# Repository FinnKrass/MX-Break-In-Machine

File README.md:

# MX Style Switch Break In Machine

Repository is still a work in progress!

A unique take on the switch break in machine intended to streamline the process and maximise outcomes. Useful for those who want to improve the sound and feeling of MX style keyboard switches that come scratchy/inconsistent from the factory.

**Table of Contents:**

- [Main README](#mx-style-switch-break-in-machine)
  
  - [Background](#background)
  
  - [Features](#features)
  
  - [To Do](#to-do)
  
  - [References & Thanks](#references--thanks)

- [Bill of Materials - Hardware](https://github.com/FinnKrass/MX-Break-In-Machine/blob/main/BoM/Bill-of-Materials-(Hardware).md#bill-of-materials-hardware)
  
  - [Hardware](https://github.com/FinnKrass/MX-Break-In-Machine/blob/main/BoM/Bill-of-Materials-(Hardware).md#hardware)
  
  - [Fasteners](https://github.com/FinnKrass/MX-Break-In-Machine/blob/main/BoM/Bill-of-Materials-(Hardware).md#fasteners)

- [Making Your Own](https://github.com/FinnKrass/MX-Break-In-Machine/blob/main/Documentation/Making-Your-Own.md#making-your-own)
  
  - [Printing](https://github.com/FinnKrass/MX-Break-In-Machine/blob/main/Documentation/Making-Your-Own.md#printing)
    
    - [Print BoM](https://github.com/FinnKrass/MX-Break-In-Machine/blob/main/Documentation/Making-Your-Own.md#print-bom)
  
  - [Additional Hardware](https://github.com/FinnKrass/MX-Break-In-Machine/blob/main/Documentation/Making-Your-Own.md#additional-hardware)
    
    - [Fasteners](https://github.com/FinnKrass/MX-Break-In-Machine/blob/main/Documentation/Making-Your-Own.md#fasteners)
  
  - [Assembly](https://github.com/FinnKrass/MX-Break-In-Machine/blob/main/Documentation/Making-Your-Own.md#assembly)
    
    - [Tools Needed](https://github.com/FinnKrass/MX-Break-In-Machine/blob/main/Documentation/Making-Your-Own.md#tools-needed)
    
    - [Prepare Motor & Limit Switch](https://github.com/FinnKrass/MX-Break-In-Machine/blob/main/Documentation/Making-Your-Own.md#preparing-the-motor--limit-switch)
    
    - [Prepare Motor Assembly](https://github.com/FinnKrass/MX-Break-In-Machine/blob/main/Documentation/Making-Your-Own.md#prepare-the-motor-assembly)
    
    - [Prepare the Pistons](https://github.com/FinnKrass/MX-Break-In-Machine/blob/main/Documentation/Making-Your-Own.md#prepare-the-pistons)
    
    - [Install the Pistons](https://github.com/FinnKrass/MX-Break-In-Machine/blob/main/Documentation/Making-Your-Own.md#install-the-pistons)
    
    - [Install the Motor Assembly](https://github.com/FinnKrass/MX-Break-In-Machine/blob/main/Documentation/Making-Your-Own.md#install-the-motor-assembly)
    
    - [Install the PCB](https://github.com/FinnKrass/MX-Break-In-Machine/blob/main/Documentation/Making-Your-Own.md#install-the-pcb)
  
  - [Testing & Notes](https://github.com/FinnKrass/MX-Break-In-Machine/blob/main/Documentation/Making-Your-Own.md#testing--notes)

- [Making the PCB](https://github.com/FinnKrass/MX-Break-In-Machine/blob/main/Documentation/Making-The-PCB.md)
  
  - [Notes](https://github.com/FinnKrass/MX-Break-In-Machine/blob/main/Documentation/Making-The-PCB.md#notes)
  
  - [To Do](https://github.com/FinnKrass/MX-Break-In-Machine/blob/main/Documentation/Making-The-PCB.md#to-do)
  
  - [Ordering from JLCPCB](https://github.com/FinnKrass/MX-Break-In-Machine/blob/main/Documentation/Making-The-PCB.md#ordering-from-jlcpcb)

## Background

This project started when I first fell in love with Cherry MX Black's. I wanted a way to break in the switches for all of my builds, but had absolutely no understanding of electronics and CAD at the time, so took it upon myself to learn how to use Fusion360 and eventually design a circuit. Once the design had come together, I started selling broken in switches with a fleet of these machines running around the clock, which helped me vet the design and iron out any problems as well as optimize certain things to make the labor involved with operating and maintaining the machines easier. I worked on this project on and off over about a year and was planning to sell the machines themselves once they were in a state I was proud of, but some life events got in the way, so I've decided to work back and open source it for others to enjoy as much as I have.

## Features

The machine is quite rugged, I've had customers request their switches broken in for 2.5 million + actuations and the machines have handled that no problem. For good measure, I give them 1 hour break every 12 hours, and have had machines comfortably surpass total lifetime actuations of 75 million. This isn't guaranteed of course, it depends on a plethora of variables, including materials used to print, print profiles, the motor manufacturer, bearing quality etc. Regardless, here is a list of features:

- Linear bearings (inspired by Feng Studio's machine)
  
  - Eliminate plastic on plastic friction
  - Ensure the pistons remain aligned, applying even force on all switches

- Full capacity (64 switches) off centre operation.

- Noise reducing plates
  
  - The biggest issue I had with the machines was the noise. To fix that, rear plates were integrated into the design that would be printed in a flexible material (95A TPU) to dampen the noise produced by the switches colliding with the back walls and pistons.
  - An off centre version of this was introduced later on. There are two models for this; one which attaches to the piston, and one which rests against the back wall. The intention is to operate in off centre at all times.

- USB Power Delivery compatible controller & power supply.

- 128x64 OLED display for information on progress.

- Actuation counter with programmable profiles to disable/enable the motor after *x* number of actuations. Currently programmed to turn off after 250,000 actuations to ensure an even distribution of off centre actuations on all 4 sides.

- Two speeds can be selected via a switch on the PCB.

- Rugged 24V motor, capable 564 actuations/minute. (Faster is not recommended)

- Non-volatile flash memory, will recall number of actuations recorded in the event of power loss.

Here are a few video's showing off the operation. [Video A](https://youtu.be/W0hglbHXOGw), [Video B](https://youtu.be/-IIjR5GEPkg).

Some older video's of their operation can be found [here](https://youtube.com/shorts/SL5bj8C431c) and [here](https://youtube.com/shorts/yf9J68zrslU).

## To-Do

- [ ] Finalise documentation
  
  - [ ] User guide and tips on operating the machine
  
  - [ ] General clean up, more coherent structure.

- [ ] Acceptable print tolerance specifications

- [x] Piston bearing socket tolerance calibration print

- [ ] PCB BoM optimisations (more details in PCB doc)

- [ ] PCB BoM sheet for mouser to automate adding to cart (should be done very soon)

## References & Thanks

The individual who helped me most requested not to be named, but a deep thank you goes out to them for the help they have provided me and continue to provide to the community. Their help is the reason I became more interested in the intricacies of electronics, and that passion has continued far beyond this project now. 

[Kee Keen's open source break in machine](https://github.com/keekeen/MX-Switch-Break-In-Machine/tree/main) helped me greatly in the beginning, definitely check it out if you're interested in the roots of this project!

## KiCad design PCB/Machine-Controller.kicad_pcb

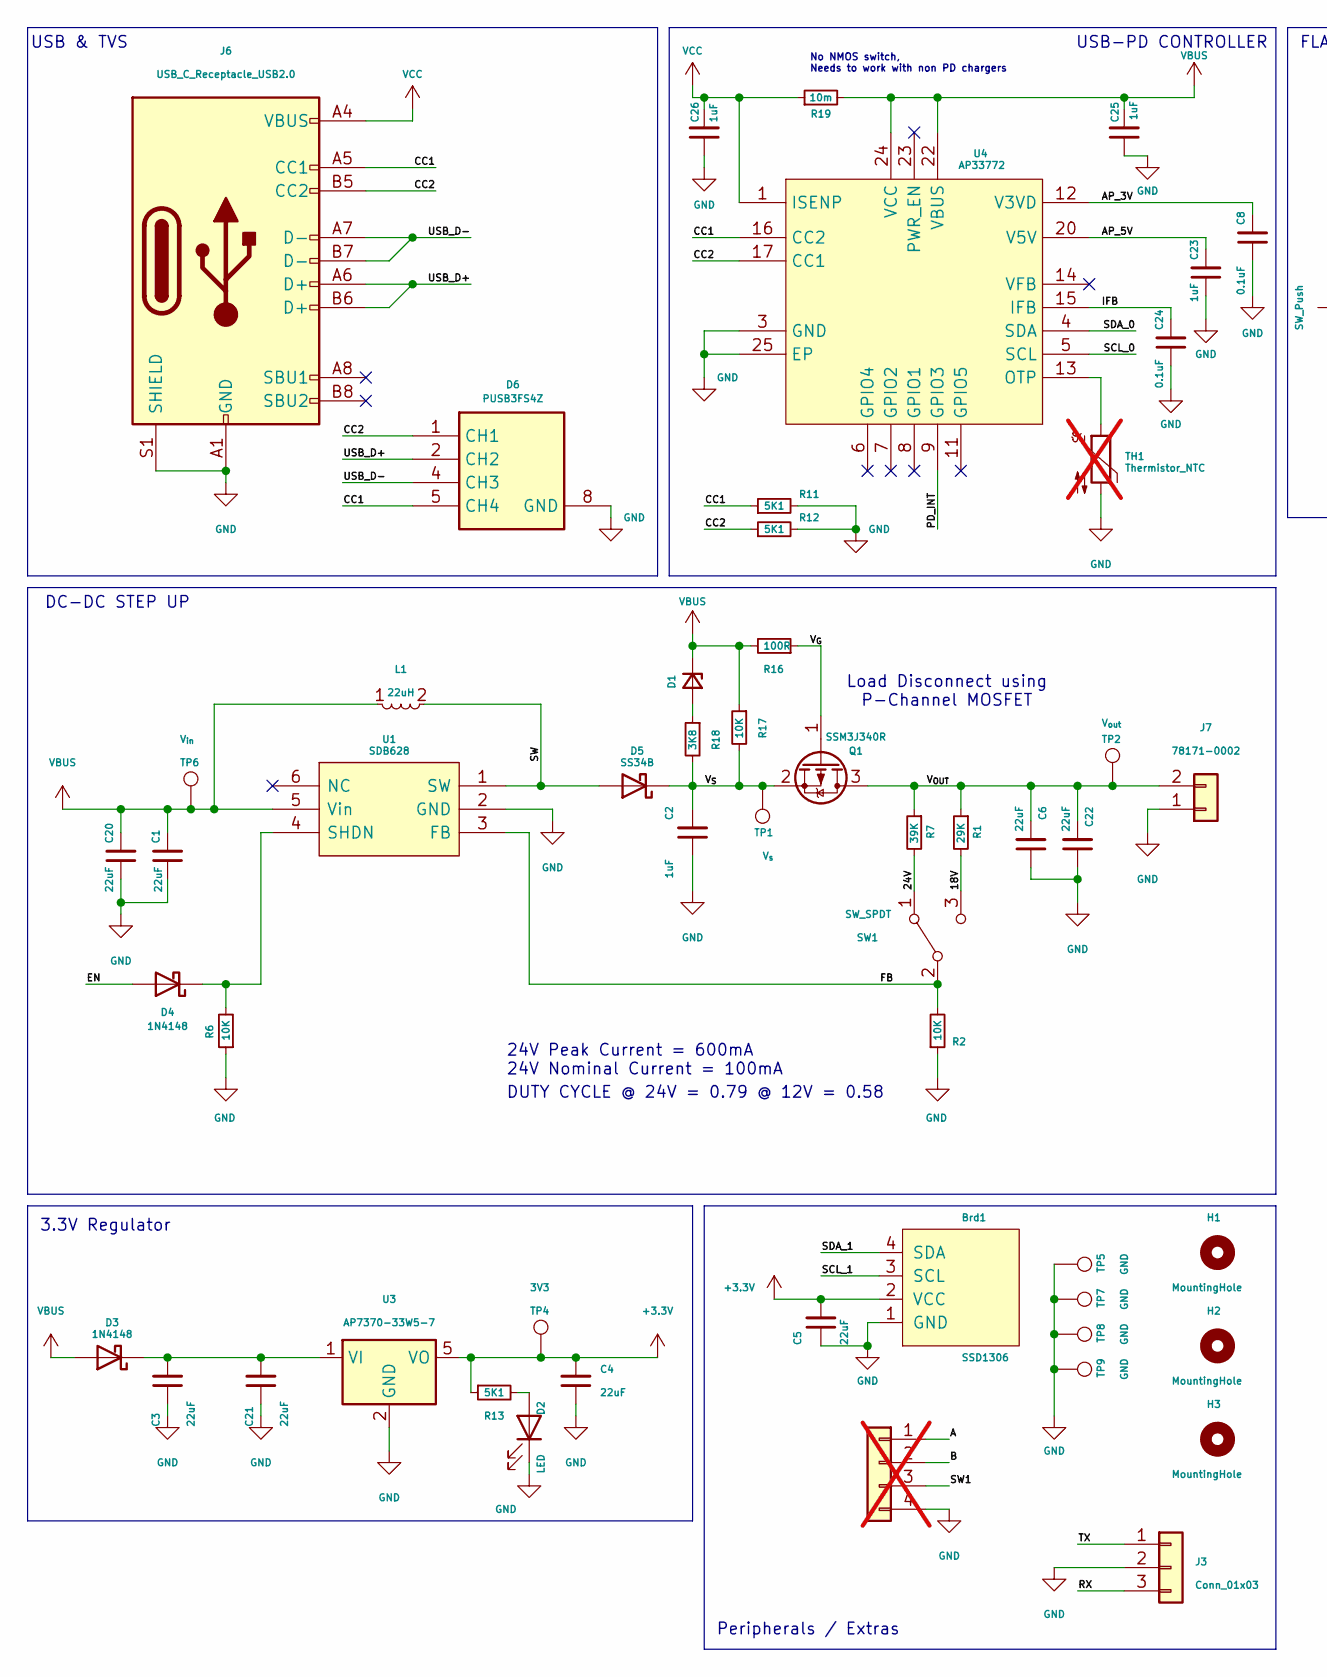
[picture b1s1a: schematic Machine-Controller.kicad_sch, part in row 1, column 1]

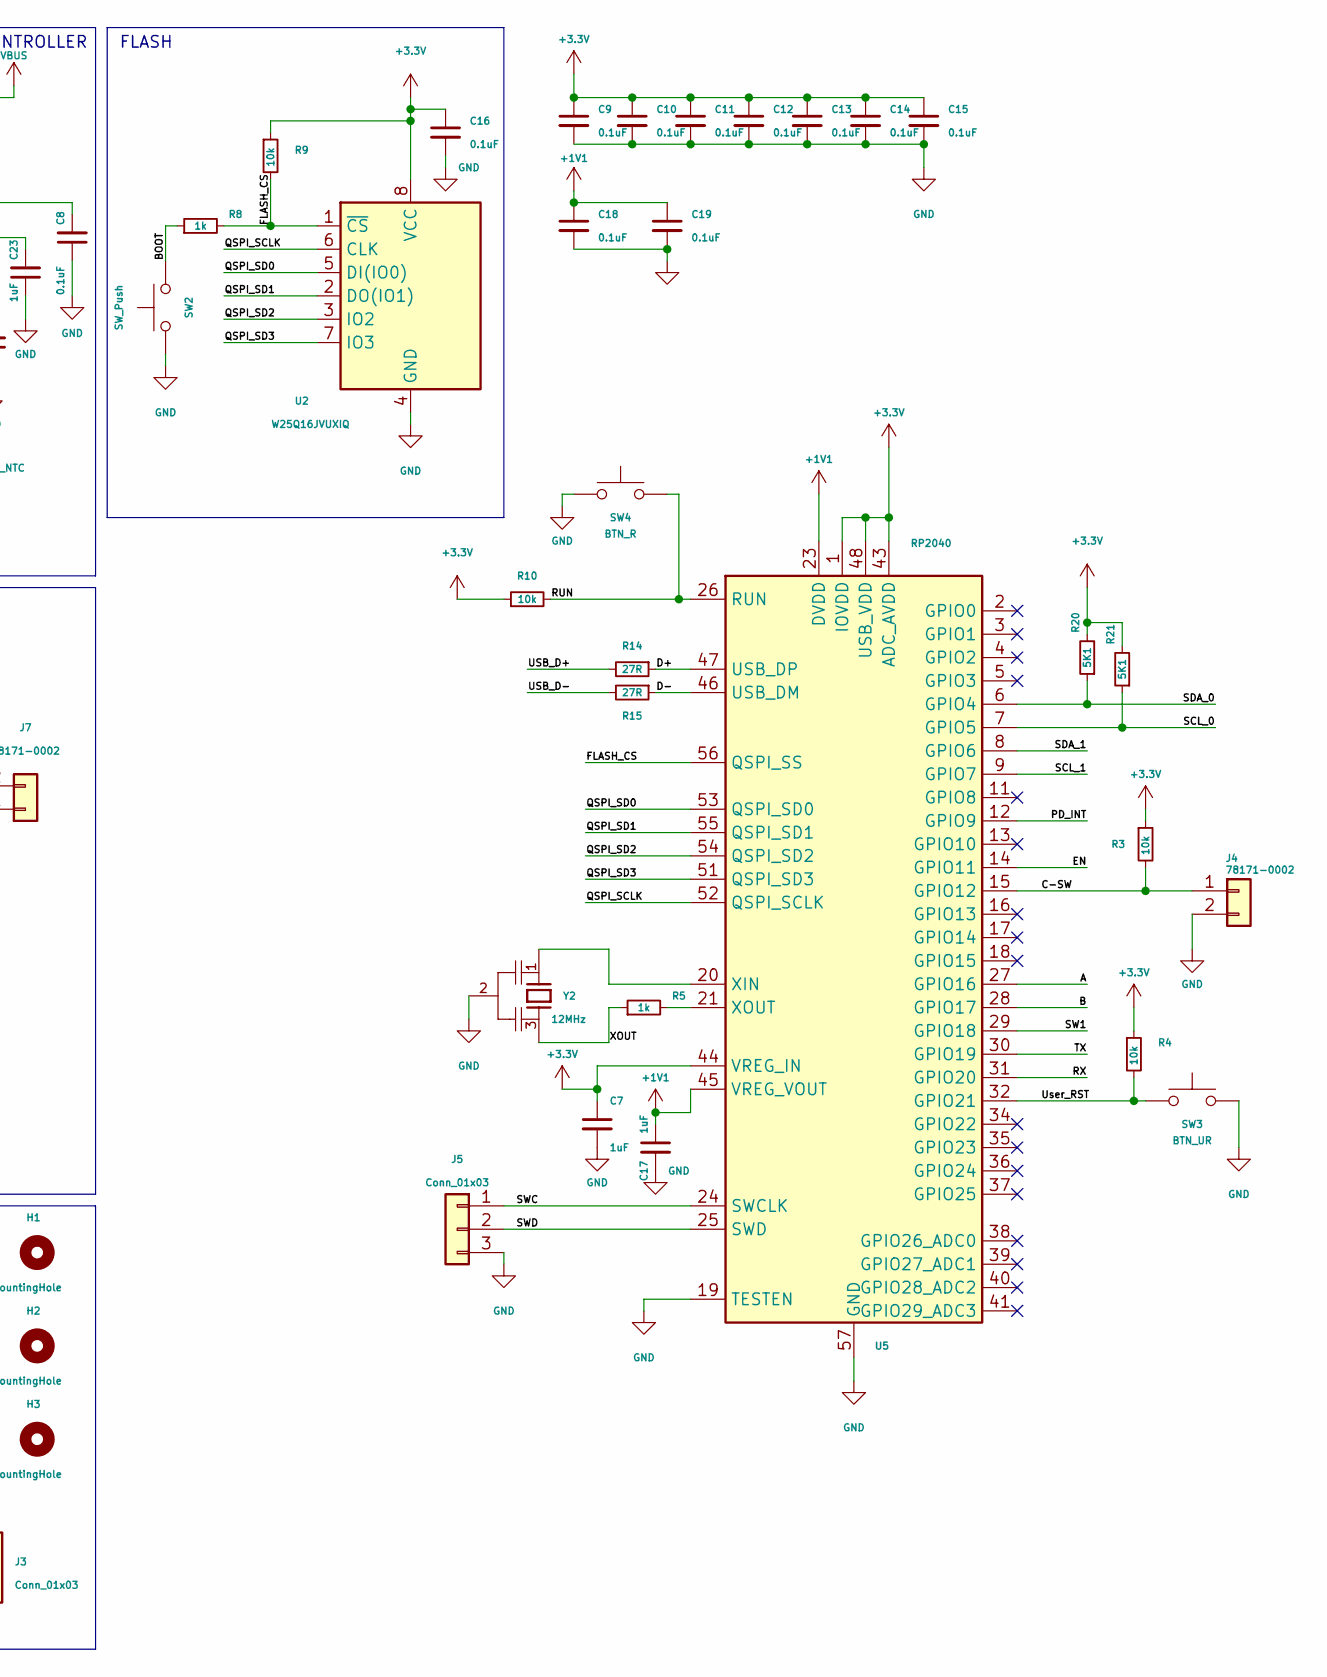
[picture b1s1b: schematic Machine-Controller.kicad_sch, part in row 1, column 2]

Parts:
Brd1: SSD1306; Display_128x64_096_I2C; Manufacturer_Part_Number SSD1306 128x66
C1, C3, C6, C20, C21, C22: 22uF; C_0805_2012Metric
C2: 1uF; C_0805_2012Metric
C4, C5: 22uF; C_0603_1608Metric
C7, C17, C23, C25, C26: 1uF; C_0603_1608Metric
C8, C9, C10, C11, C12, C13, C14, C15, C16, C18, C19, C24: 0.1uF; C_0402_1005Metric
D1: BZX84C22-7-F; SOT-23-3
D2: LED; LED_0603_1608Metric
D3, D4: 1N4148; D_SOD-323F
D5: SS34B; D_SMB
D6: PUSB3FS4Z; DFN2510A-10; Mouser Part Number 771-PUSB3FS4Z
H1, H2, H3: MountingHole; M2_Screw_PTH
J2: Conn_01x05; Molex_Pico-EZmate_78171-0004_1x04-1MP_P1.20mm_Vertical; not fitted
J3: Conn_01x03; PinSocket_1x03_P2.54mm_Vertical
J4, J7: 78171-0002; Molex_Pico-EZmate_78171-0002_1x02; Manufacturer_Part_Number 78171-0002
J5: Conn_01x03; JST_SH_BM03B-SRSS-TB_1x03-1MP_P1.00mm_Vertical
J6: USB_C_Receptacle_USB2.0; USB_C_Receptacle_HRO_TYPE-C-31-M-12; Manufacturer_Part_Number TYPE-C-31-M-12
L1: 22uH; TDK-VLS5045-5x5.3x4.5; Manufacturer_Part_Number 74438356220
Q1: SSM3J340R; SOT-23-3F
R1: 29K; R_0805_2012Metric
R2, R6, R17: 10K; R_0603_1608Metric
R3, R4, R9, R10: 10k; R_0603_1608Metric
R5, R8: 1k; R_0402_1005Metric
R7: 39K; R_0805_2012Metric
R11, R12, R13, R20, R21: 5K1; R_0603_1608Metric
R14, R15: 27R; R_0603_1608Metric
R16: 100R; R_0603_1608Metric
R18: 3K8; R_0603_1608Metric
R19: 10m; R_0603_1608Metric
SW1: SW_SPDT; SW_Slide_1P2T_CK_OS102011MS2Q
SW2: SW_Push; PinHeader_1x02_P2.00mm_Vertical
SW3: BTN_UR; SW_SPST_TL3342; Manufacturer_Part_Number TS-1187A-B-A-B
SW4: BTN_R; SW_SPST_TL3342; Manufacturer_Part_Number TS-1187A-B-A-B
TH1: Thermistor_NTC; C_0402_1005Metric; not fitted
TP1: V_{s}; Keystone_5000-5004_Miniature
TP2: V_{out}; Keystone_5000-5004_Miniature
TP4: 3V3; Keystone_5000-5004_Miniature
TP5, TP7, TP8, TP9: GND; TestPoint_THTPad_1.5x1.5mm_Drill0.7mm
TP6: V_{in}; Keystone_5000-5004_Miniature
U1: SDB628; SOT-23-6; Manufacturer_Part_Number SDB628
U2: W25Q16JVUXIQ; USON-8_2x3x0.6mm; Manufacturer_Part_Number W25Q16JVUXIQ
U3: AP7370-33W5-7; SOT-23-5
U4: AP33772; QFN50P400X400X80-25N-D; Mouser Part Number 621-AP33772DKZ-13
U5: RP2040; RP2040-QFN-56
Y2: 12MHz; OSC_CSTNE12M0G520000R0; PARTREV JGC42-8858A

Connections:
+1V1: C17.1, C18.1, C19.1, U5.23 (DVDD), U5.45 (VREG_VOUT), U5.50 (DVDD)
+3.3V: Brd1.2 (VCC), C4.2, C5.2, C7.1, C9.1, C10.1, C11.1, C12.1, C13.1, C14.1, C15.1, C16.1, R3.1, R4.1, R9.1, R10.1, R13.1, R20.2, R21.2, TP4.1, U2.8 (VCC), U3.5 (VO), U5.1 (IOVDD), U5.10 (IOVDD), U5.22 (IOVDD), U5.33 (IOVDD), U5.42 (IOVDD), U5.43 (ADC_AVDD), U5.44 (VREG_IN), U5.48 (USB_VDD), U5.49 (IOVDD)
/18V: R1.2, SW1.3 (C)
/24V: R7.2, SW1.1 (A)
/A: J2.1, U5.27 (GPIO16)
/AP_3V: C8.2, U4.12 (V3VD)
/AP_5V: C23.2, U4.20 (V5V)
/B: J2.2, U5.28 (GPIO17)
/BOOT: R8.1, SW2.2
/C-SW: J4.1, R3.2, U5.15 (GPIO12)
/CC1: D6.5 (CH4), D6.6 (NC1), J6.A5 (CC1), R11.1, U4.16 (CC2)
/CC2: D6.1 (CH1), D6.10 (NC4), J6.B5 (CC2), R12.1, U4.17 (CC1)
/D+: R14.1, U5.47 (USB_DP)
/D-: R15.1, U5.46 (USB_DM)
/EN: D4.2 (A), U5.14 (GPIO11)
/FB: R2.2, SW1.2 (B), U1.3 (FB)
/FLASH_CS: R8.2, R9.2, U2.1 (~CS), U5.56 (QSPI_SS)
/IFB: C24.2, U4.15 (IFB)
/PD_INT: U4.9 (GPIO3), U5.12 (GPIO9)
/QSPI_SCLK: U2.6 (CLK), U5.52 (QSPI_SCLK)
/QSPI_SD0: U2.5 (DI(IO0)), U5.53 (QSPI_SD0)
/QSPI_SD1: U2.2 (DO(IO1)), U5.55 (QSPI_SD1)
/QSPI_SD2: U2.3 (IO2), U5.54 (QSPI_SD2)
/QSPI_SD3: U2.7 (IO3), U5.51 (QSPI_SD3)
/RUN: R10.2, SW4.2, U5.26 (RUN)
/RX: J3.3, U5.31 (GPIO20)
/SCL_0: R21.1, U4.5 (SCL), U5.7 (GPIO5)
/SCL_1: Brd1.3 (SCL), U5.9 (GPIO7)
/SDA_0: R20.1, U4.4 (SDA), U5.6 (GPIO4)
/SDA_1: Brd1.4 (SDA), U5.8 (GPIO6)
/SW: D5.2 (A), L1.2, U1.1 (SW)
/SW1: J2.3, U5.29 (GPIO18)
/SWC: J5.1, U5.24 (SWCLK)
/SWD: J5.2, U5.25 (SWD)
/TX: J3.1, U5.30 (GPIO19)
/USB_D+: D6.2 (CH2), D6.9 (NC3), J6.A6 (D+), J6.B6 (D+), R14.2
/USB_D-: D6.4 (CH3), D6.7 (NC2), J6.A7 (D-), J6.B7 (D-), R15.2
/User_RST: R4.2, SW3.1, U5.32 (GPIO21)
/V_{G}: Q1.1 (G), R16.1
/V_{OUT}: C6.2, C22.2, J7.2, Q1.3 (D), R1.1, R7.1, TP2.1
/V_{S}: C2.2, D5.1 (K), Q1.2 (S), R17.2, R18.2, TP1.1
/XOUT: R5.1, Y2.3
GND: Brd1.1 (GND), C1.1, C2.1, C3.1, C4.1, C5.1, C6.1, C7.2, C8.1, C9.2, C10.2, C11.2, C12.2, C13.2, C14.2, C15.2, C16.2, C17.2, C18.2, C19.2, C20.1, C21.1, C22.1, C23.1, C24.1, C25.1, C26.1, D2.1 (K), D6.3 (GND), D6.8 (GND), J2.4, J3.2, J4.2, J5.3, J6.A1 (GND), J6.A12 (GND), J6.B1 (GND), J6.B12 (GND), J6.S1 (SHIELD), J7.1, R2.1, R6.1, R11.2, R12.2, SW2.1, SW3.2, SW4.1, TH1.2, TP5.1, TP7.1, TP8.1, TP9.1, U1.2 (GND), U2.4 (GND), U3.2 (GND), U4.3 (GND), U4.25 (EP), U5.19 (TESTEN), U5.57 (GND), Y2.2
unnamed: D1.1 (A), R18.1
unnamed: D2.2 (A), R13.2
unnamed: C3.2, C21.2, D3.1 (K), U3.1 (VI)
unnamed: D4.1 (K), R6.2, U1.4 (SHDN)
unnamed: TH1.1, U4.13 (OTP)
unnamed: U5.20 (XIN), Y2.1
unnamed: R5.2, U5.21 (XOUT)
VBUS: C1.2, C20.2, C25.2, D1.2 (NC), D1.3 (K), D3.2 (A), L1.1, R16.2, R17.1, R19.2, TP6.1, U1.5 (Vin), U4.22 (VBUS), U4.24 (VCC)
VCC: C26.2, J6.A4 (VBUS), J6.A9 (VBUS), J6.B4 (VBUS), J6.B9 (VBUS), R19.1, U4.1 (ISENP)

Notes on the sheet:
Peripherals / Extras
3.3V Regulator
No NMOS switch, Needs to work with non PD chargers
DUTY CYCLE @ 24V = 0.79 @ 12V = 0.58
USB & TVS
Load Disconnect using P-Channel MOSFET
DC-DC STEP UP
USB-PD CONTROLLER
FLASH
24V Peak Current = 600mA 24V Nominal Current = 100mA

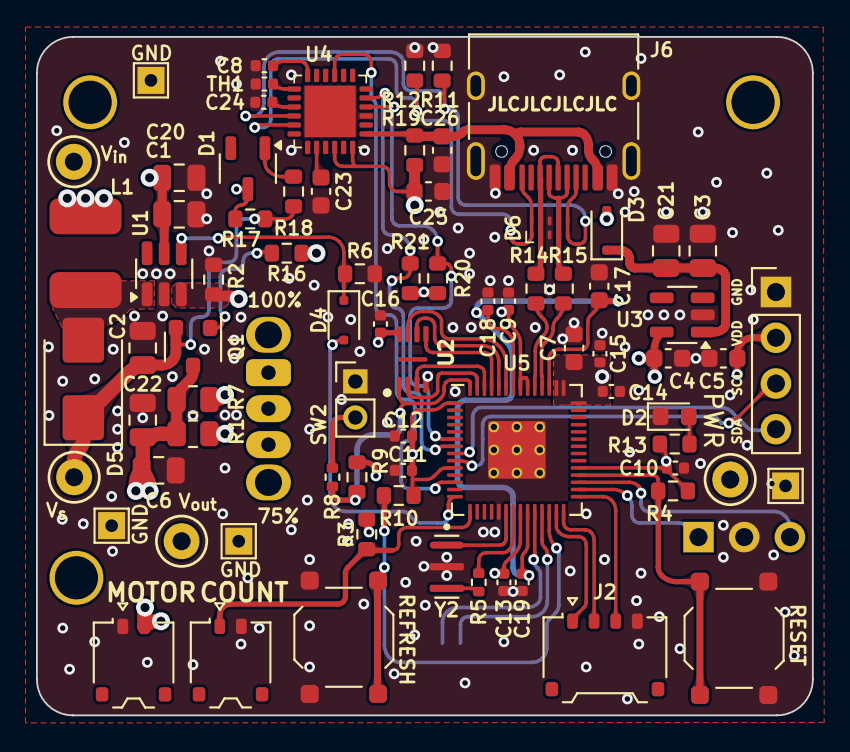
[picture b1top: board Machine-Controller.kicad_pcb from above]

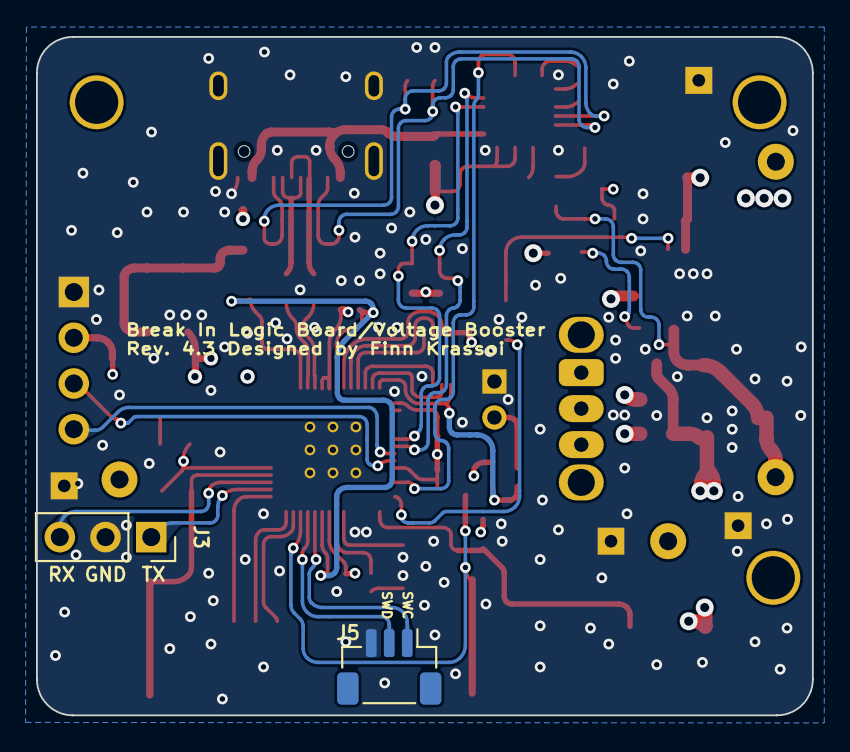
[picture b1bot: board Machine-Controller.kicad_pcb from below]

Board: 4 copper layers, 43.1 x 37.7 mm, 84 parts (2 on the bottom side), 52 nets.

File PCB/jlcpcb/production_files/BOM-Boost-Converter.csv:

Comment,Designator,Footprint,LCSC
22uF,C4,C_0603_1608Metric,
29K,R1,R_0805_2012Metric,
10k,R9,R_0402_1005Metric,
SDB628,PS1,SOT-23_SDB628,
0.1uF,C18,C_0402_1005Metric,
SSD1306,Brd1,Display_128x64_096_I2C,
22uF,C1,C_0805_2012Metric,
0.1uF,C16,C_0402_1005Metric,
0.1uF,C14,C_0402_1005Metric,
10K,R2,R_0805_2012Metric,
1uF,C17,C_0603_1608Metric,
0.1uF,C15,C_0402_1005Metric,
10k,R4,R_0402_1005Metric,
1uF,C7,C_0603_1608Metric,
39K,R7,R_0805_2012Metric,
0.1uF,C11,C_0402_1005Metric,
0.1uF,C9,C_0402_1005Metric,
0.1uF,C13,C_0402_1005Metric,
0.1uF,C12,C_0402_1005Metric,
1k,R5,R_0402_1005Metric,
0.1uF,C19,C_0402_1005Metric,
0.1uF,C10,C_0402_1005Metric,
10k,R3,R_0402_1005Metric,
1uF,C2,C_0805_2012Metric,
1k,R8,R_0402_1005Metric,
22uF,C3,C_0805_2012Metric,
10k,R10,R_0402_1005Metric,
SW_Push,SW2,PinHeader_1x02_P2.00mm_Vertical,
RESET,J1,SW_SPST_TL3342,
USB_C_Receptacle_USB2.0,J6,USB_C_Receptacle_HRO_TYPE-C-31-M-12,
W25Q32JVSS,U2,W25Q16FWUXIE,
5K1,R11,R_0402_1005Metric,
22uH,L1,TDK-VLS5045-5x5.3x4.5,
27R,R14,R_0603_1608Metric,
LED,D2,LED_0603_1608Metric,
SW_Push,SW3,SW_SPST_TL3342,
5K1,R13,R_0603_1608Metric,
22uF,C21,C_0805_2012Metric,
FerriteBead,FBr1,C_0805_2012Metric,
22uF,C20,C_0805_2012Metric,
12MHz,Y2,OSC_CSTNE12M0G520000R0,
22uF,C22,C_0805_2012Metric,
27R,R15,R_0603_1608Metric,
5K1,R12,R_0402_1005Metric,
MountingHole,H1,M2_Screw_PTH,
MountingHole,H3,M2_Screw_PTH,
MountingHole,H2,M2_Screw_PTH,
Conn_01x02,J4,Molex_Pico-EZmate_78171-0002_1x02,
SW_SPDT,SW1,SW_Slide_1P2T_CK_OS102011MS2Q,
D_Schottky,D3,D_SOD-323F,
Conn_01x05,J2,Molex_Pico-EZmate_78171-0004_1x04-1MP_P1.20mm_Vertical,
Conn_01x03,J3,PinSocket_1x03_P2.54mm_Vertical,
3V3,TP4,Keystone_5000-5004_Miniature,
"
SSM3J340R",Q1,SOT-23-3F,
GND,TP8,TestPoint_THTPad_1.5x1.5mm_Drill0.7mm,
V_{in},TP6,Keystone_5000-5004_Miniature,
100R,R16,R_0603_1608Metric,
OUTPUT,J7,Molex_Pico-EZmate_78171-0002_1x02,
V_{out},TP2,Keystone_5000-5004_Miniature,
GND,TP9,TestPoint_THTPad_1.5x1.5mm_Drill0.7mm,
22uF,C5,C_0603_1608Metric,
GND,TP5,TestPoint_THTPad_1.5x1.5mm_Drill0.7mm,
D_Schottky,D4,D_SOD-323F,
10K,R6,R_0402_1005Metric,
SS34B,D5,D_SMB,
V_{s},TP1,Keystone_5000-5004_Miniature,
GND,TP7,TestPoint_THTPad_1.5x1.5mm_Drill0.7mm,
10K,R17,R_0603_1608Metric,
Conn_01x03,J5,JST_SH_BM03B-SRSS-TB_1x03-1MP_P1.00mm_Vertical,
22V,D1,SOT-23-3,
AP33772,U4,QFN50P400X400X80-25N-D,
Thermistor_NTC,TH1,C_0402_1005Metric,
AP7370-33W5-7,U3,SOT-23-5,
RP2040,U5,RP2040-QFN-56,
22uF,C6,C_0805_2012Metric,
100nF,C8,C_0402_1005Metric,
1uF,C23,C_0402_1005Metric,
10m,R19,R_0603_1608Metric,
100nF,C24,C_0402_1005Metric,
5K1,R21,R_0603_1608Metric,
3K8,R18,R_0603_1608Metric,
5K1,R20,R_0603_1608Metric,
PUSB3FS4Z,D6,DFN2510A-10,
1uF,C25,C_0603_1608Metric,
1uF,C26,C_0603_1608Metric,

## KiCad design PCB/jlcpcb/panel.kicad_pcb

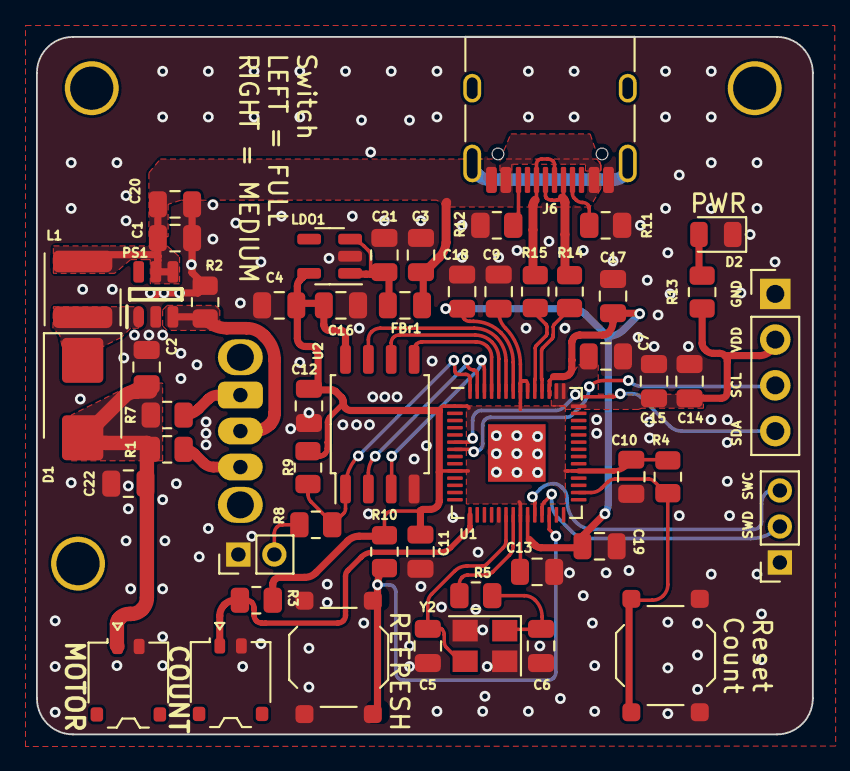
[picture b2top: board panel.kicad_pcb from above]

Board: 2 copper layers, 43.1 x 38.8 mm, 56 parts (0 on the bottom side), 34 nets.

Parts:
Brd1: SSD1306; Display_128x64_096_I2C
C1, C2, C3, C4, C20, C21, C22: 22uF; C_0805_2012Metric
C5, C6: 22pF; C_0805_2012Metric
C7, C17: 1uF; C_0805_2012Metric
C9, C10, C11, C12, C13, C14, C15, C16, C18, C19: 0.1uF; C_0805_2012Metric
D1: SS34B-HF; D_SMB
D2: LED; LED_0805_2012Metric
FBr1: FerriteBead; C_0805_2012Metric
H1, H2, H3: MountingHole; M2_Screw_PTH
J1: RESET; SW_SPST_TL3342
J2: Conn_01x03; PinSocket_1x03_P2.00mm_Vertical
J4: Conn_01x02; Molex_Pico-EZmate_78171-0002_1x02-1MP_P1.20mm_Vertical
J6: USB_C_Receptacle_USB2.0; USB_C_Receptacle_HRO_TYPE-C-31-M-12
L1: 22uH; L_Wurth_WE-LQSH-4020
LDO1: TCR2EF33,LM_CT; SOT-23-5
OUTPUT1: OUTPUT; Molex_Pico-EZmate_78171-0002_1x02-1MP_P1.20mm_Vertical
PS1: SDB628
R1: 31k; R_0805_2012Metric
R2: 2K2; R_0805_2012Metric
R3, R4, R10: 10k; R_0805_2012Metric
R5, R8: 1k; R_0805_2012Metric
R7: 42k; R_0805_2012Metric
R9: 10K; R_0805_2012Metric
R11, R12, R13: 5K1; R_0805_2012Metric
R14, R15: 27Ohm; R_0805_2012Metric
SW1: SW_SPDT; SW_Slide_1P2T_CK_OS102011MS2Q
SW2: SW_Push; PinHeader_1x02_P2.00mm_Vertical
SW3: SW_Push; SW_SPST_TL3342
U1: RP2040; QFN-56-1EP_7x7mm_P0.4mm_EP3.2x3.2mm
U2: W25Q32JVSS; SOIC-8_5.23x5.23mm_P1.27mm
Y2: 12MHz; Crystal_SMD_3225-4Pin_3.2x2.5mm

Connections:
+1V1: C17.1, C18.1, C19.1, U1.23 (DVDD), U1.45 (VREG_VOUT), U1.50 (DVDD)
+3.3V: Brd1.2 (VCC), C4.2, C7.1, C9.1, C10.1, C11.1, C12.1, C13.1, C14.1, C15.1, C16.1, LDO1.5 (VOUT), R3.1, R4.1, R9.1, R10.1, R13.1, U1.1 (IOVDD), U1.10 (IOVDD), U1.22 (IOVDD), U1.33 (IOVDD), U1.42 (IOVDD), U1.43 (ADC_AVDD), U1.44 (VREG_IN), U1.48 (USB_VDD), U1.49 (IOVDD), U2.8 (VCC)
/9V: R1.2, SW1.3 (C)
/12V: R7.2, SW1.1 (A)
/BOOT: R8.1, SW2.2
/C-SW: J4.1, R3.2, U1.15 (GPIO12)
/FB: PS1.3 (FB), R2.2, SW1.2 (B)
/RUN: J1.2, R10.2, U1.26 (RUN)
/Reset: R4.2, SW3.1, U1.30 (GPIO19)
/SCL: Brd1.3 (SCL), U1.7 (GPIO5)
/SDA: Brd1.4 (SDA), U1.6 (GPIO4)
/SW: D1.1, L1.2, PS1.1 (SW)
/SWCLK: J2.3, U1.24 (SWCLK)
/SWD: J2.2, U1.25 (SWD)
/USB_D+: J6.A6 (D+), J6.B6 (D+), R15.2
/USB_D-: J6.A7 (D-), J6.B7 (D-), R14.2
/VOUT: C2.2, C22.2, D1.2, OUTPUT1.1, R1.1, R7.1
/XIN: C5.2, U1.20 (XIN), Y2.3
/XOUT: C6.2, R5.1, Y2.1
D+: R15.1, U1.47 (USB_DP)
D-: R14.1, U1.46 (USB_DM)
GND: Brd1.1 (GND), C1.1, C2.1, C3.1, C4.1, C5.1, C6.1, C7.2, C9.2, C10.2, C11.2, C12.2, C13.2, C14.2, C15.2, C16.2, C17.2, C18.2, C19.2, C20.1, C21.1, C22.1, D2.1 (K), J1.1, J2.1, J4.2, J6.A1 (GND), J6.A12 (GND), J6.B1 (GND), J6.B12 (GND), LDO1.2 (GND), OUTPUT1.2, PS1.2 (GND), R2.1, R11.2, R12.2, SW2.1, SW3.2, U1.19 (TESTEN), U1.57 (GND), U2.4 (GND), Y2.2, Y2.4
unnamed: D2.2 (A), R13.2
unnamed: J6.A5 (CC1), R11.1
unnamed: J6.B5 (CC2), R12.1
unnamed: C21.2, FBr1.2, LDO1.1 (VIN), LDO1.3 (CONTROL)
unnamed: R5.2, U1.21 (XOUT)
QSPI_SCLK: U1.52 (QSPI_SCLK), U2.6 (CLK)
QSPI_SD0: U1.53 (QSPI_SD0), U2.5 (DI(IO0))
QSPI_SD1: U1.55 (QSPI_SD1), U2.2 (DO(IO1))
QSPI_SD2: U1.54 (QSPI_SD2), U2.3 (IO2)
QSPI_SD3: U1.51 (QSPI_SD3), U2.7 (IO3)
QSPI_SS: R8.2, R9.2, U1.56 (QSPI_SS), U2.1 (~CS)
VCC: C1.2, C3.2, C20.2, FBr1.1, J6.A4 (VBUS), J6.A9 (VBUS), J6.B4 (VBUS), J6.B9 (VBUS), L1.1, PS1.4 (EN), PS1.5 (IN)

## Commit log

2024-05-31 silkscreen
2024-06-01 add 3D models
2024-06-01 images
2024-06-01 photo
2024-06-01 readme
2024-06-02 docs and images
2024-06-02 docs
2024-06-02 graphs
2024-06-02 license
2024-06-05 BoM and Docs
2024-06-16 more docs
2024-06-16 so many docs
2024-06-16 calibration stl
2024-06-16 pic test
2024-06-16 resize pics
2024-06-16 vids
2024-06-17 Fixes malformed links in BOM
    added missing `https://` prefix that was causing AE links to 404 when viewing on github as markdown.
2024-06-18 Fixed Bug in FW
2024-06-18 typo
